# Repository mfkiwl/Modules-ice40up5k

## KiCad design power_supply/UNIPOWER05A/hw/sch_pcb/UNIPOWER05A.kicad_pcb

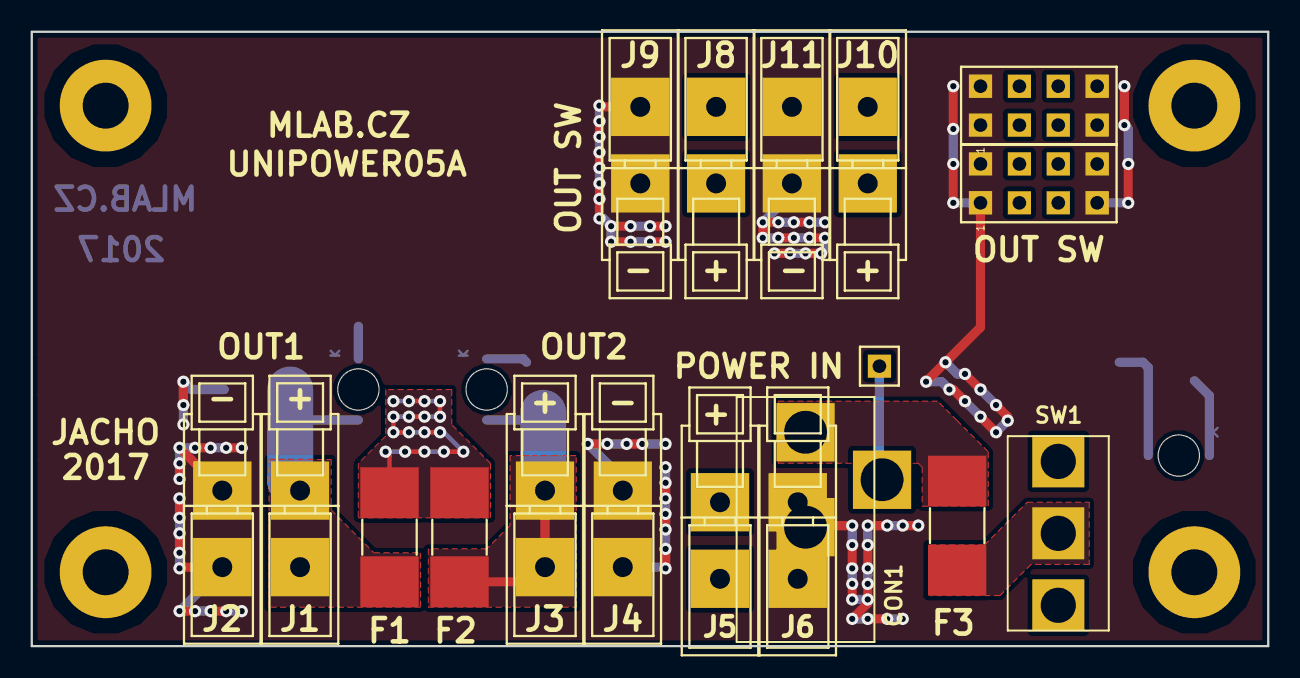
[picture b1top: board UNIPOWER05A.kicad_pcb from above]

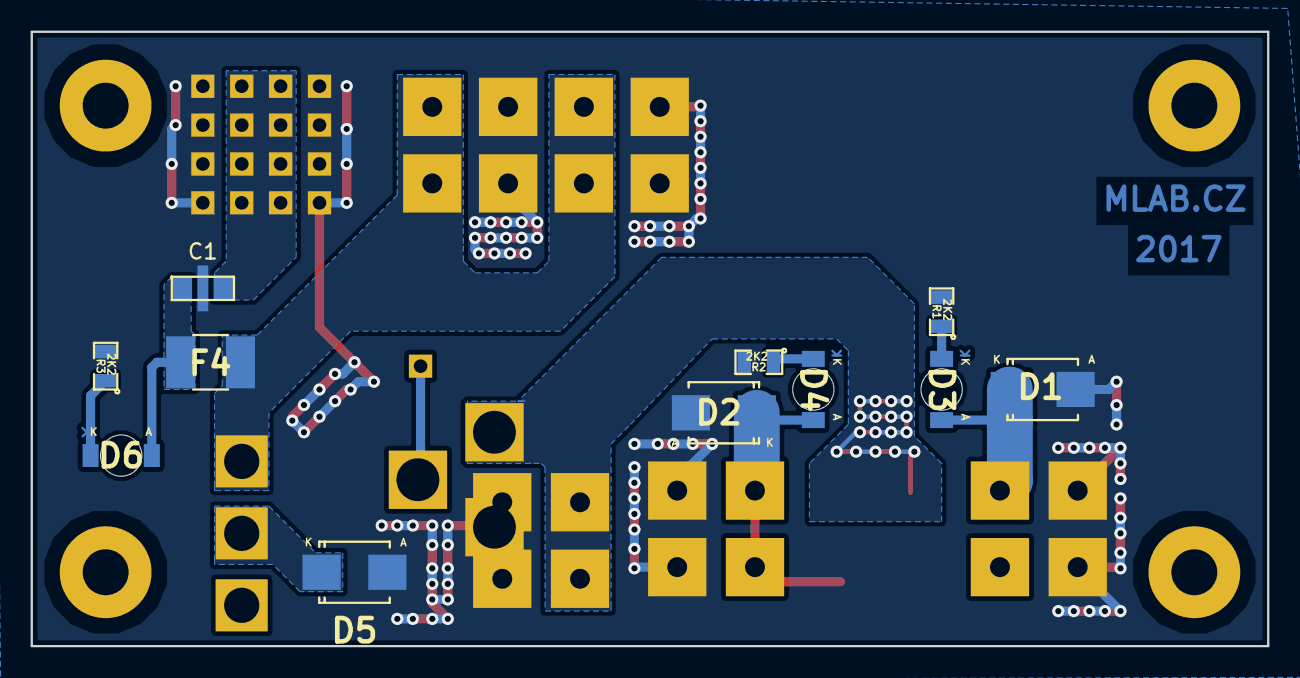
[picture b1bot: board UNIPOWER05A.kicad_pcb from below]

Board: 2 copper layers, 80.8 x 40.1 mm, 33 parts (11 on the bottom side), 12 nets.

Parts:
C1: NFM21PC105; FIR1
CON1: JACK_DC2.1; DC2,1MM
D1, D2, D5: SMBJ15A-E3/52; SMB_Standard
D3, D4, D6: RED; LED_1206
F1, F2, F3: 5A; Drzak_2410
F4: 1.1A; 1812
J1, J2, J3, J4, J5, J6, J8, J9, J10, J11: CONN1_1; WAGO256
J7: CONN1_1; Straight_1x01
J12, J13: JUMP_4X2; Straight_2x04
P1, P2, P3, P4: _; MountingHole_3mm
R1, R2, R3: 2K2; SMD-0805
SW1: Prepinac; Prepinaci_3A_SL19121

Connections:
GND: C1.2, CON1.2, D1.2, D2.2, D5.2, J2.1, J4.1, J6.1, J9.1, J11.1, J12.1, J12.2, J12.7, J12.8, J13.1, J13.2, J13.7, J13.8, R1.2, R2.2, R3.2
unnamed: C1.1, D6.2, F4.1
unnamed: C1.3, J12.3, J12.4, J12.5, J12.6, J13.3, J13.4, J13.5, J13.6
unnamed: CON1.1, F1.1, F2.1, F3.2, J5.1
unnamed: CON1.3, J7.1
unnamed: D1.1, D3.2, F1.2, J1.1
unnamed: D2.1, D4.2, F2.2, J3.1
unnamed: D3.1, R1.1
unnamed: D4.1, R2.1
unnamed: D5.1, F3.1, SW1.2
unnamed: D6.1, R3.1
unnamed: F4.2, J8.1, J10.1, SW1.1
